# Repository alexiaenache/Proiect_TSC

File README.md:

# 📖 OpenBook – E-Reader cu ESP32-C6

**-TSC-**  
Alexia-Ioana Enache – 331CA

---

## 🧠 Arhitectură generală

Sistemul reprezintă un cititor digital inteligent, construit în jurul microcontrollerului **ESP32-C6**, optimizat pentru consum redus și interacțiune minimă din partea utilizatorului, având ca scop principal afișarea eficientă de conținut pe un ecran E-Ink.

---

## 🧩 Componente principale și funcționalitate

### 1. ESP32-C6 – Unitatea centrală de control
- **Funcție:** Coordonează toate componentele, gestionează afișajul și comunicația.
- **Caracteristici cheie:**
  - Procesor RISC-V performant.
  - Suport Wi-Fi 6 (802.11ax) pentru actualizări sau funcționalitate în rețea.
  - Moduri avansate de economisire a energiei (deep sleep, modem sleep).

---

### 2. Afișaj E-Ink
- **Tip:** Ecran monocrom (ex. 2.9"), optimizat pentru citire.
- **Control:** Prin interfață SPI, cu linii dedicate de comandă (CS, DC, RST, BUSY).
- **Beneficii:** Consum de curent extrem de redus între refresh-uri – ideal pentru aplicații de tip e-paper.

---

### 3. Senzor de mediu – BME688
- **Scop:** Monitorizare temperatură, umiditate, presiune și calitatea aerului.
- **Conectivitate:** I2C (implicit) sau SPI (alternativ).
- **Consum:** µA în stand-by, câțiva mA în funcționare activă.

---

### 4. Ceas în timp real – DS3231
- **Funcționalitate:** Menține ora exactă, ideal pentru time-stamping sau notificări programate.
- **Interfață:** I2C + pin de alarmă (INT/SQW).
- **Consum:** Sub 2 µA în menținerea ceasului pe baterie.

---

### 5. Memorie SPI – W25Q512 (64Mbit NOR Flash)
- **Rol:** Depozitare pentru fișiere, cărți, date configurabile.
- **Protocol:** SPI, suportând frecvențe mari pentru transfer rapid.
- **Eficiență energetică:** Consumă doar în timpul operațiunilor active.

---

### 6. Sistem de alimentare
- **USB-C:** Intrare de 5V pentru alimentare și comunicație.
- **Încărcare baterie:** MCP73831 controlează încărcarea Li-Po, cu curent reglat prin rezistor (ex. 500mA).
- **Conversie tensiune:**
  - **LDO / DC-DC:** Reglează 3.7V de la baterie la 3.3V pentru întreaga platformă.
  - Opțional: step-up DC-DC pentru a obține 5V dacă e necesar.

---

### 7. Control fizic – Butoane SMD
- 3 butoane dedicate: Boot, Reset și Funcțional.
- Legate la GPIO-uri configurate cu pull-up/pull-down.
- Logica de debounce poate fi software sau hardware.

---

### 8. Alte funcționalități
- Protecții ESD aplicate pe liniile critice: USB, SPI, I2C, alimentare.
- **Test Pads**: Acces facil la semnale importante (MISO, MOSI, SCK, RX, TX, GND, 3V3) pentru depanare sau programare externă.

---

## 🛠️ Considerații hardware (PCB Design)

### Rutare & alimentare:
- **Trasee de putere:** Minim 0.3 mm pentru 3V3, 5V, VBAT.
- **Linii de semnal:** Minim 0.15 mm pentru SPI, I2C, UART etc.
- **Grosime PCB:** Ideal < 1 mm pentru carcase compacte.

### Decuplare & stabilitate:
- Condensatoare **100nF** (0402) pentru fiecare pin VCC.
- Condensatoare **4.7 µF - 10 µF** pentru stabilizarea LDO și surse locale.

### Antenă ESP32-C6:
- Zona antenei trebuie eliberată de cupru (decupaj în GND + semnale), conform datasheetului Espressif.

### DRC/ ERC:
- Verificări obligatorii:
  - Unghiuri ≤ 45°.
  - Planuri GND corect cusute cu via stitching.
  - Clearance și distanțe respectate conform producătorului.

### Layout:
- Componente doar pe **Top Layer** (SMD).
- USB-C și butoanele poziționate ergonomic și accesibil.

### Test Pad-uri:
- Expunere pentru debug, programare și validare semnale: 3V3, GND, RX, TX, SPI.

---
## 📐 Diagrama bloc

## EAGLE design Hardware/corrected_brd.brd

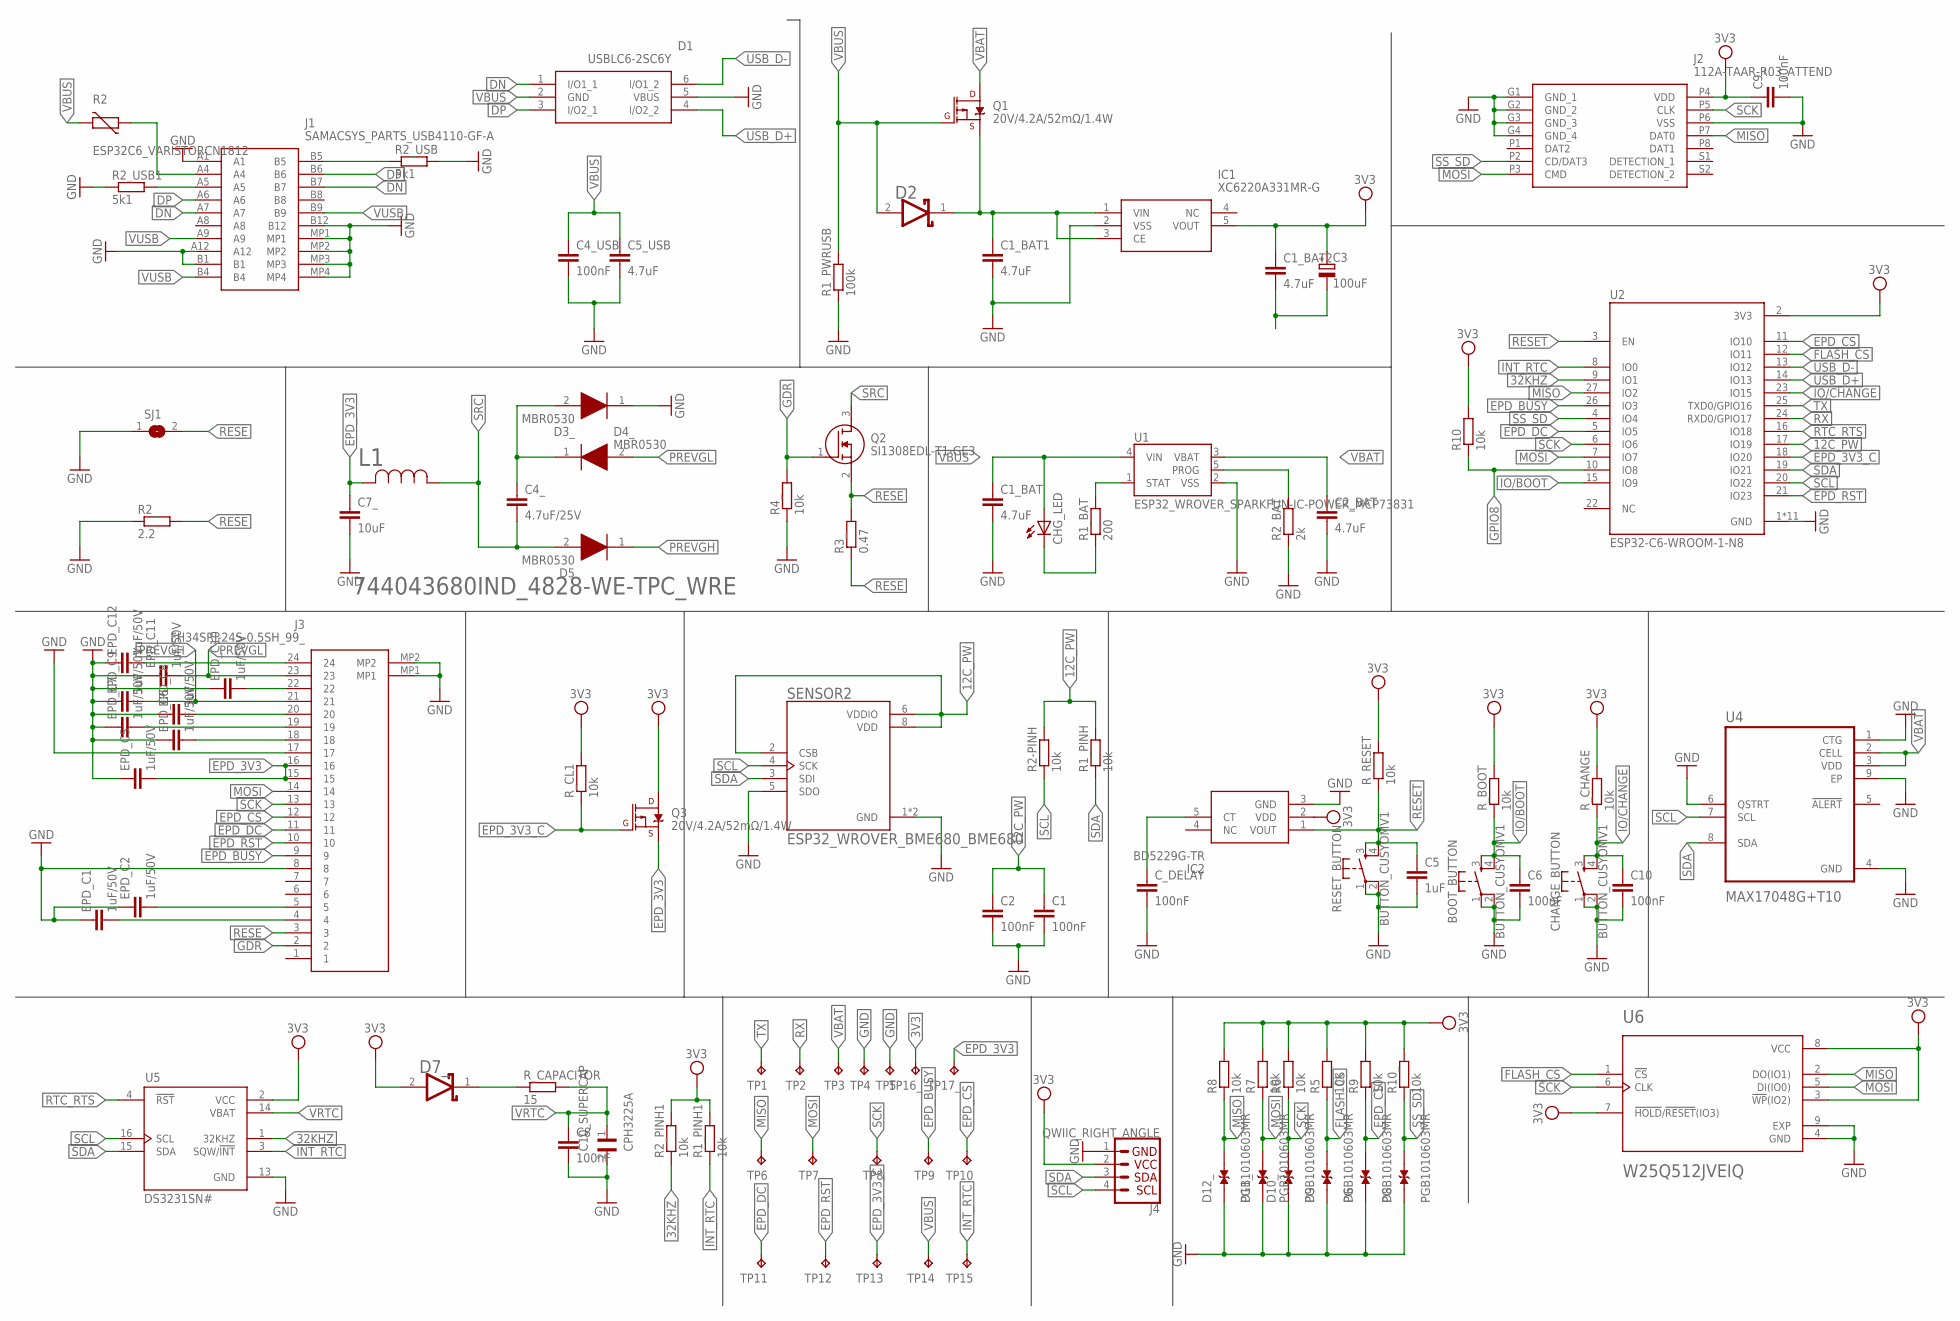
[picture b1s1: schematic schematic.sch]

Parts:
BOOT_BUTTON: BUTTON_CUSYOMV1; MYBUTTON
C1, C2, C4_USB, C8: 100nF; EAGLE-LTSPICE_C0402
C1_BAT, C1_BAT1, C1_BAT2, C2_BAT, C5_USB: 4.7uF; EAGLE-LTSPICE_C0402
C3: 100uF; RCL_CT3528
C4_: 4.7uF/25V; EAGLE-LTSPICE_C0402
C5: 1uF; EAGLE-LTSPICE_C0402
C6, C9_, C10: 100nF; ESP32_WROVER_EAGLE-LTSPICE_C0402
C7_: 10uF; EAGLE-LTSPICE_C0402
C10_SUPERCAP: CPH3225A; CAPCP3225X100N
CHANGE_BUTTON: BUTTON_CUSYOMV1; MYBUTTON
CHG_LED: ADAFRUIT_LEDCHIP-LED0603; ADAFRUIT_CHIP-LED0603
C_DELAY: 100nF; EAGLE-LTSPICE_C0402
D1: USBLC6-2SC6Y; SOT95P280X145-6N
D2, D7_: ESP32_WROVER_AVX---SD0805S020S1R0_AVX_SD0805S020S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; ESP32_WROVER_AVX---SD0805S020S1R0_AVX_SD0805S020S1R0_0
D3_, D4_, D5: MBR0530; SOD3716X135N
D6, D8, D9, D10_, D11_, D12_: PGB1010603MR; DIOC1608X36N
EPD_C1, EPD_C2, EPD_C5, EPD_C6, EPD_C7, EPD_C8, EPD_C9, EPD_C10, EPD_C11, EPD_C12: 1uF/50V; EAGLE-LTSPICE_C0402
IC1: XC6220A331MR-G; SOT95P280X120-5N
IC2: BD5229G-TR; SOT95P280X125-5N
J1: SAMACSYS_PARTS_USB4110-GF-A; SAMACSYS_PARTS_USB4110GFA
J2: 112A-TAAR-R03_ATTEND; 112ATAARR03ATTEND
J3: FH34SRJ-24S-0.5SH_99_; FH34SRJ24S05SH99
J4: QWIIC_RIGHT_ANGLE; JST04_1MM_RA
L1: 744043680IND_4828-WE-TPC_WRE; IND_4828-WE-TPC_WRE
Q1, Q3: 20V/4.2A/52mΩ/1.4W; ESP32_WROVER_SPARKFUN-DISCRETESEMI_SOT23-3
Q2: SI1308EDL-T1-GE3; SOT65P210X110-3N
R1_BAT: 200; ESP32_WROVER_EAGLE-LTSPICE_R0402
R1_PINH, R1_PINH1, R2-PINH, R2_PINH1, R4_, R5, R6, R7, R8, R9, R10, R10_: 10k; ESP32_WROVER_EAGLE-LTSPICE_R0402
R1_PWRUSB: 100k; ESP32_WROVER_EAGLE-LTSPICE_R0402
R2: ESP32C6_VARISTORCN1812; ESP32C6_VARISTOR_CT/CN1812
R2_: 2.2; ESP32_WROVER_EAGLE-LTSPICE_R0402
R2_BAT: 2k; ESP32_WROVER_EAGLE-LTSPICE_R0402
R2_USB, R2_USB1: 5k1; ESP32_WROVER_EAGLE-LTSPICE_R0402
R3_: 0.47; ESP32_WROVER_EAGLE-LTSPICE_R0402
RESET_BUTTON: BUTTON_CUSYOMV1; MYBUTTON
R_BOOT: 10k; ESP32_WROVER_EAGLE-LTSPICE_R0402
R_CAPACITOR: 15; ESP32_WROVER_EAGLE-LTSPICE_R0402
R_CHANGE: 10k; ESP32_WROVER_EAGLE-LTSPICE_R0402
R_CL1: 10k; ESP32_WROVER_EAGLE-LTSPICE_R0402
R_RESET: 10k; ESP32_WROVER_EAGLE-LTSPICE_R0402
SENSOR2: ESP32_WROVER_BME680_BME680; ESP32_WROVER_BME680_PSON80P300X300X100-8N
SJ1: SJ
TP1, TP2, TP3, TP4, TP5, TP6, TP7, TP8, TP9, TP10, TP11, TP12, TP13, TP14, TP15, TP16_, TP17_: TPTP20R; TP20R
U1: ESP32_WROVER_SPARKFUN-IC-POWER_MCP73831; ESP32_WROVER_SPARKFUN-IC-POWER_SOT23-5
U2: ESP32-C6-WROOM-1-N8; XCVR_ESP32-C6-WROOM-1-N8
U4: MAX17048G+T10; SON50P200X200X80-9N
U5: DS3231SN#; SOIC127P1032X265-16N
U6: W25Q512JVEIQ; SON127P600X800X80-9N

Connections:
3V3: C1_BAT2.1, C3.+, C9_.1, D7_.2 (ANODE), IC1.5 (VOUT), IC2.2 (VDD), J2.P4 (VDD), J4.2, Q3.3 (D), R1_PINH1.2, R2_PINH1.2, R5.2, R6.2, R7.2, R8.2, R9.2, R10.2, R10_.2, R_BOOT.2, R_CHANGE.2, R_CL1.2, R_RESET.2, TP16_.TP, U2.2 (3V3), U5.2 (VCC), U6.3 (!WP!(IO2)), U6.7 (!HOLD!/!RESET!(IO3)), U6.8 (VCC)
12C_PW: C1.1, C2.1, R1_PINH.2, R2-PINH.2, SENSOR2.2 (CSB), SENSOR2.6 (VDDIO), SENSOR2.8 (VDD), U2.17 (IO19)
32KHZ: R2_PINH1.1, U2.9 (IO1), U5.1 (32KHZ)
DN: D1.1 (I/O1_1), J1.A7, J1.B7
DP: D1.3 (I/O2_1), J1.A6, J1.B6
EPD_3V3: C7_.1, EPD_C5.2, J3.15, J3.16, L1.2, Q3.2 (S), TP17_.TP
EPD_3V3_C: Q3.1 (G), R_CL1.1, TP13.TP, U2.18 (IO20)
EPD_BUSY: J3.9, TP9.TP, U2.26 (IO3)
EPD_CS: D6.2, J3.12, R9.1, TP10.TP, U2.11 (IO10)
EPD_DC: J3.11, TP11.TP, U2.5 (IO5)
EPD_RST: J3.10, TP12.TP, U2.21 (IO23)
FLASH_CS: D9.2, R5.1, U2.12 (IO11), U6.1 (!CS)
GDR: J3.2, Q2.1 (G), R4_.2
GND: BOOT_BUTTON.1, BOOT_BUTTON.2, C1.2, C1_BAT.2, C1_BAT1.2, C2.2, C2_BAT.2, C4_USB.2, C5.2, C5_USB.2, C6.2, C7_.2, C8.2, C9_.2, C10.2, C10_SUPERCAP.2, CHANGE_BUTTON.1, CHANGE_BUTTON.2, C_DELAY.2, D1.5 (VBUS), D3_.1 (K), D6.1, D8.1, D9.1, D10_.1, D11_.1, D12_.1, EPD_C1.1, EPD_C2.1, EPD_C5.1, EPD_C6.1, EPD_C7.1, EPD_C8.1, EPD_C9.1, EPD_C10.1, EPD_C11.1, EPD_C12.1, IC1.2 (VSS), IC2.3 (GND), J1.A1, J1.A12, J1.B1, J1.B12, J1.MP1, J1.MP2, J1.MP3, J1.MP4, J2.G1 (GND_1), J2.G2 (GND_2), J2.G3 (GND_3), J2.G4 (GND_4), J2.P6 (VSS), J3.8, J3.17, J3.MP1, J3.MP2, J4.1, R1_PWRUSB.1, R2_.1, R2_BAT.1, R2_USB.2, R2_USB1.1, R4_.1, RESET_BUTTON.1, RESET_BUTTON.2, SENSOR2.1 (GND), SENSOR2.5 (SDO), SENSOR2.7 (GND), SJ1.1, TP4.TP, TP5.TP, U1.2 (VSS), U2.1 (GND), U2.28 (GND), U2.29_1 (GND), U2.29_2 (GND), U2.29_3 (GND), U2.29_4 (GND), U2.29_5 (GND), U2.29_6 (GND), U2.29_7 (GND), U2.29_8 (GND), U2.29_9 (GND), U4.1 (CTG), U4.4 (GND), U4.6 (QSTRT), U4.9 (EP), U5.13 (GND), U6.4 (GND), U6.9 (EXP)
GPIO8: R10.1, U2.10 (IO8)
INT_RTC: R1_PINH1.1, TP15.TP, U2.8 (IO0), U5.3 (SQW/!INT)
IO/BOOT: BOOT_BUTTON.3, BOOT_BUTTON.4, C6.1, R_BOOT.1, U2.15 (IO9)
IO/CHANGE: C10.1, CHANGE_BUTTON.3, CHANGE_BUTTON.4, R_CHANGE.1, U2.23 (IO15)
MISO: D12_.2, J2.P7 (DAT0), R8.1, TP6.TP, U2.27 (IO2), U6.2 (DO(IO1))
MOSI: D11_.2, J2.P3 (CMD), J3.14, R7.1, TP7.TP, U2.7 (IO7), U6.5 (DI(IO0))
unnamed: J1.A4, R2.1
unnamed: J1.A5, R2_USB1.2
unnamed: J1.B5, R2_USB.1
unnamed: C1_BAT1.1, D2.1 (CATHODE), IC1.1 (VIN), IC1.3 (CE), Q1.2 (S)
unnamed: C4_.1, D3_.2 (A), D4_.1 (K)
unnamed: C1_BAT2.2, C3.-
unnamed: EPD_C12.2, J3.24
unnamed: EPD_C1.2, J3.4
unnamed: C_DELAY.1, IC2.5 (CT)
unnamed: R2_BAT.2, U1.5 (PROG)
unnamed: EPD_C2.2, J3.5
unnamed: EPD_C10.2, J3.22
unnamed: D7_.1 (CATHODE), R_CAPACITOR.1
unnamed: R1_BAT.2, U1.1 (STAT)
unnamed: CHG_LED.C, R1_BAT.1
unnamed: EPD_C8.2, J3.20
unnamed: EPD_C7.2, J3.19
unnamed: EPD_C6.2, J3.18
PREVGH: D5.1 (K), EPD_C9.2, J3.21
PREVGL: D4_.2 (A), EPD_C11.2, J3.23
RESE: J3.3, Q2.2 (S), R2_.2, R3_.1, R3_.2, SJ1.2
RESET: C5.1, IC2.1 (VOUT), RESET_BUTTON.3, RESET_BUTTON.4, R_RESET.1, U2.3 (EN)
RTC_RTS: U2.16 (IO18), U5.4 (!RST)
RX: TP2.TP, U2.24 (RXD0/GPIO17)
SCK: D10_.2, J2.P5 (CLK), J3.13, R6.1, TP8.TP, U2.6 (IO6), U6.6 (CLK)
SCL: J4.4, R2-PINH.1, SENSOR2.4 (SCK), U2.20 (IO22), U4.7 (SCL), U5.16 (SCL)
SDA: J4.3, R1_PINH.1, SENSOR2.3 (SDI), U2.19 (IO21), U4.8 (SDA), U5.15 (SDA)
SRC: C4_.2, D5.2 (A), L1.1, Q2.3 (D)
SS_SD: D8.2, J2.P2 (CD/DAT3), R10_.1, U2.4 (IO4)
TX: TP1.TP, U2.25 (TXD0/GPIO16)
USB_D+: D1.4 (I/O2_2), U2.14 (IO13)
USB_D-: D1.6 (I/O1_2), U2.13 (IO12)
VBAT: C2_BAT.1, Q1.3 (D), TP3.TP, U1.3 (VBAT), U4.2 (CELL), U4.3 (VDD)
VBUS: C1_BAT.1, C4_USB.1, C5_USB.1, CHG_LED.A, D1.2 (GND), D2.2 (ANODE), Q1.1 (G), R1_PWRUSB.2, R2.2, TP14.TP, U1.4 (VIN)
VRTC: C8.1, C10_SUPERCAP.1, R_CAPACITOR.2, U5.14 (VBAT)
VUSB: J1.A9, J1.B4, J1.B9

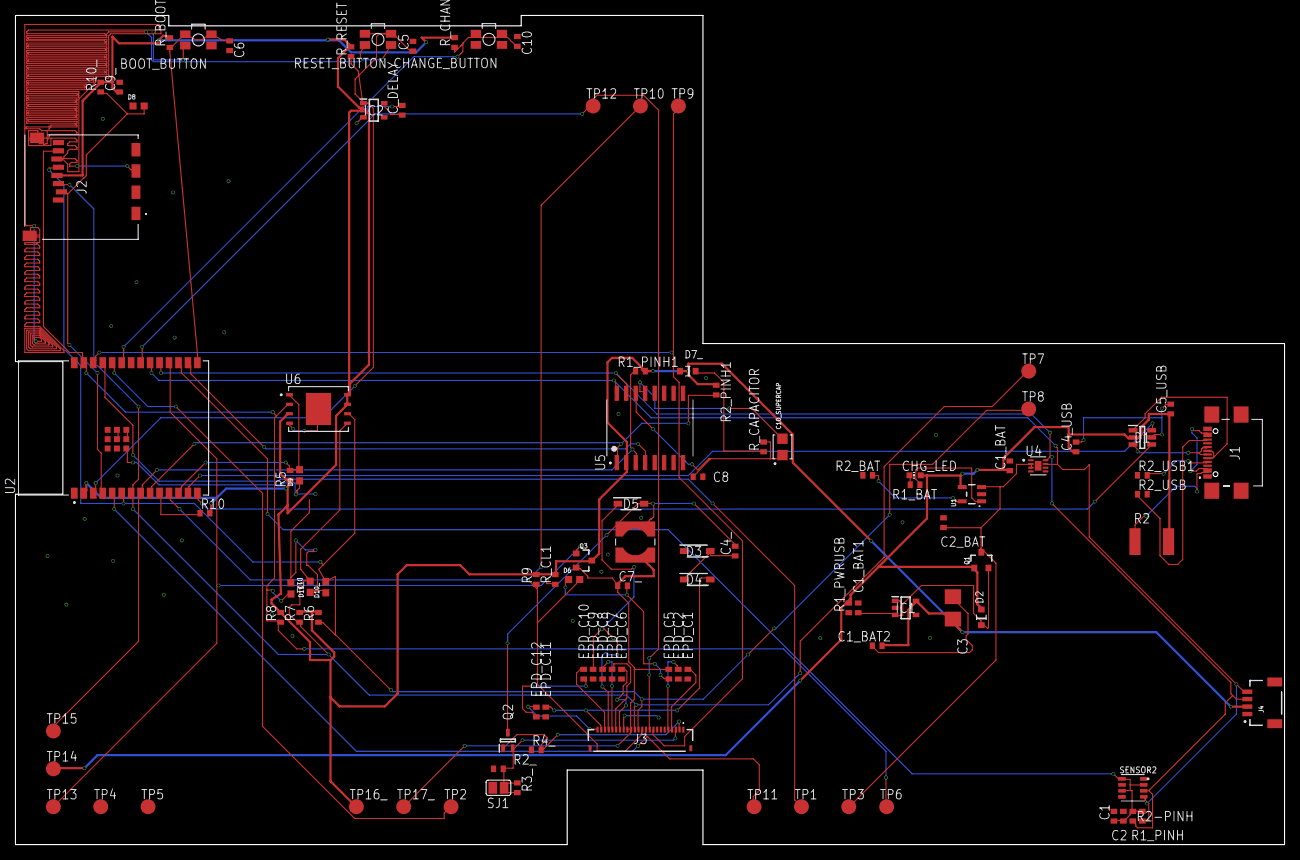
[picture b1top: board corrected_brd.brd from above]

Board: 2 copper layers, 170.2 x 111.2 mm, 103 parts (0 on the bottom side), 56 nets.

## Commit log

2025-04-13 added corrected brd
2025-04-14 README.md

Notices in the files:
parts and their libraries:
COPYRIGHT: Copyright (C) 2024 Ultra Librarian. All rights reserved.
